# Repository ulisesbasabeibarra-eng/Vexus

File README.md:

# Triatlon-2026
Robot Triatlón para Bonaerenses 2026 por parte de los Alumnos de 6° año. **Campeones Región 2**

- [@Ulises Basabe](https://github.com/ulisesbasabeibarra-eng)
- [@Facundo Dominguez](https://github.com/facundodominguez1)
- [@Ramiro Trejo](https://github.com/RamiiTrejo)

## Componentes 

1-Esp32 38 pines

1-Bateria 2s de 450mAh

1-Bateria 3s de 1050mAh

2-Driver de motores BTS7960

2-Motores Titán de 1000RPM

## Sensores
1-Regleta **QTR8a** [Datasheet]()

3-Sensores infrarrojos **TCRT5000** [Datasheet]()

5-Sensores **Sharp Gp2y0a02yk0f**: [Datasheet]()

-3 frontales

-2 laterales

## PCB

Este PCB fue realizado con el software de diseño libre y gratuito KiCad, el cual nos facilita el uso debido a su interfaz intuitiva 

En este se implemento el diseño doble faz y componentes SMD (como lo son capacitores, una resitencia y un regulador)

## Modelo 3D

En este proyecto se utilizo Autodesk, plataforma de software, ademas de ser muy utilizado a la hora de hacer diseños 3D, gracias a que este ofrece una amplia gama de software como AutoCAD, Fusion 360, Inventor y 3ds Max, utilizados en sectores como la ingeniería, la arquitectura, el entretenimiento y el diseño de productos.

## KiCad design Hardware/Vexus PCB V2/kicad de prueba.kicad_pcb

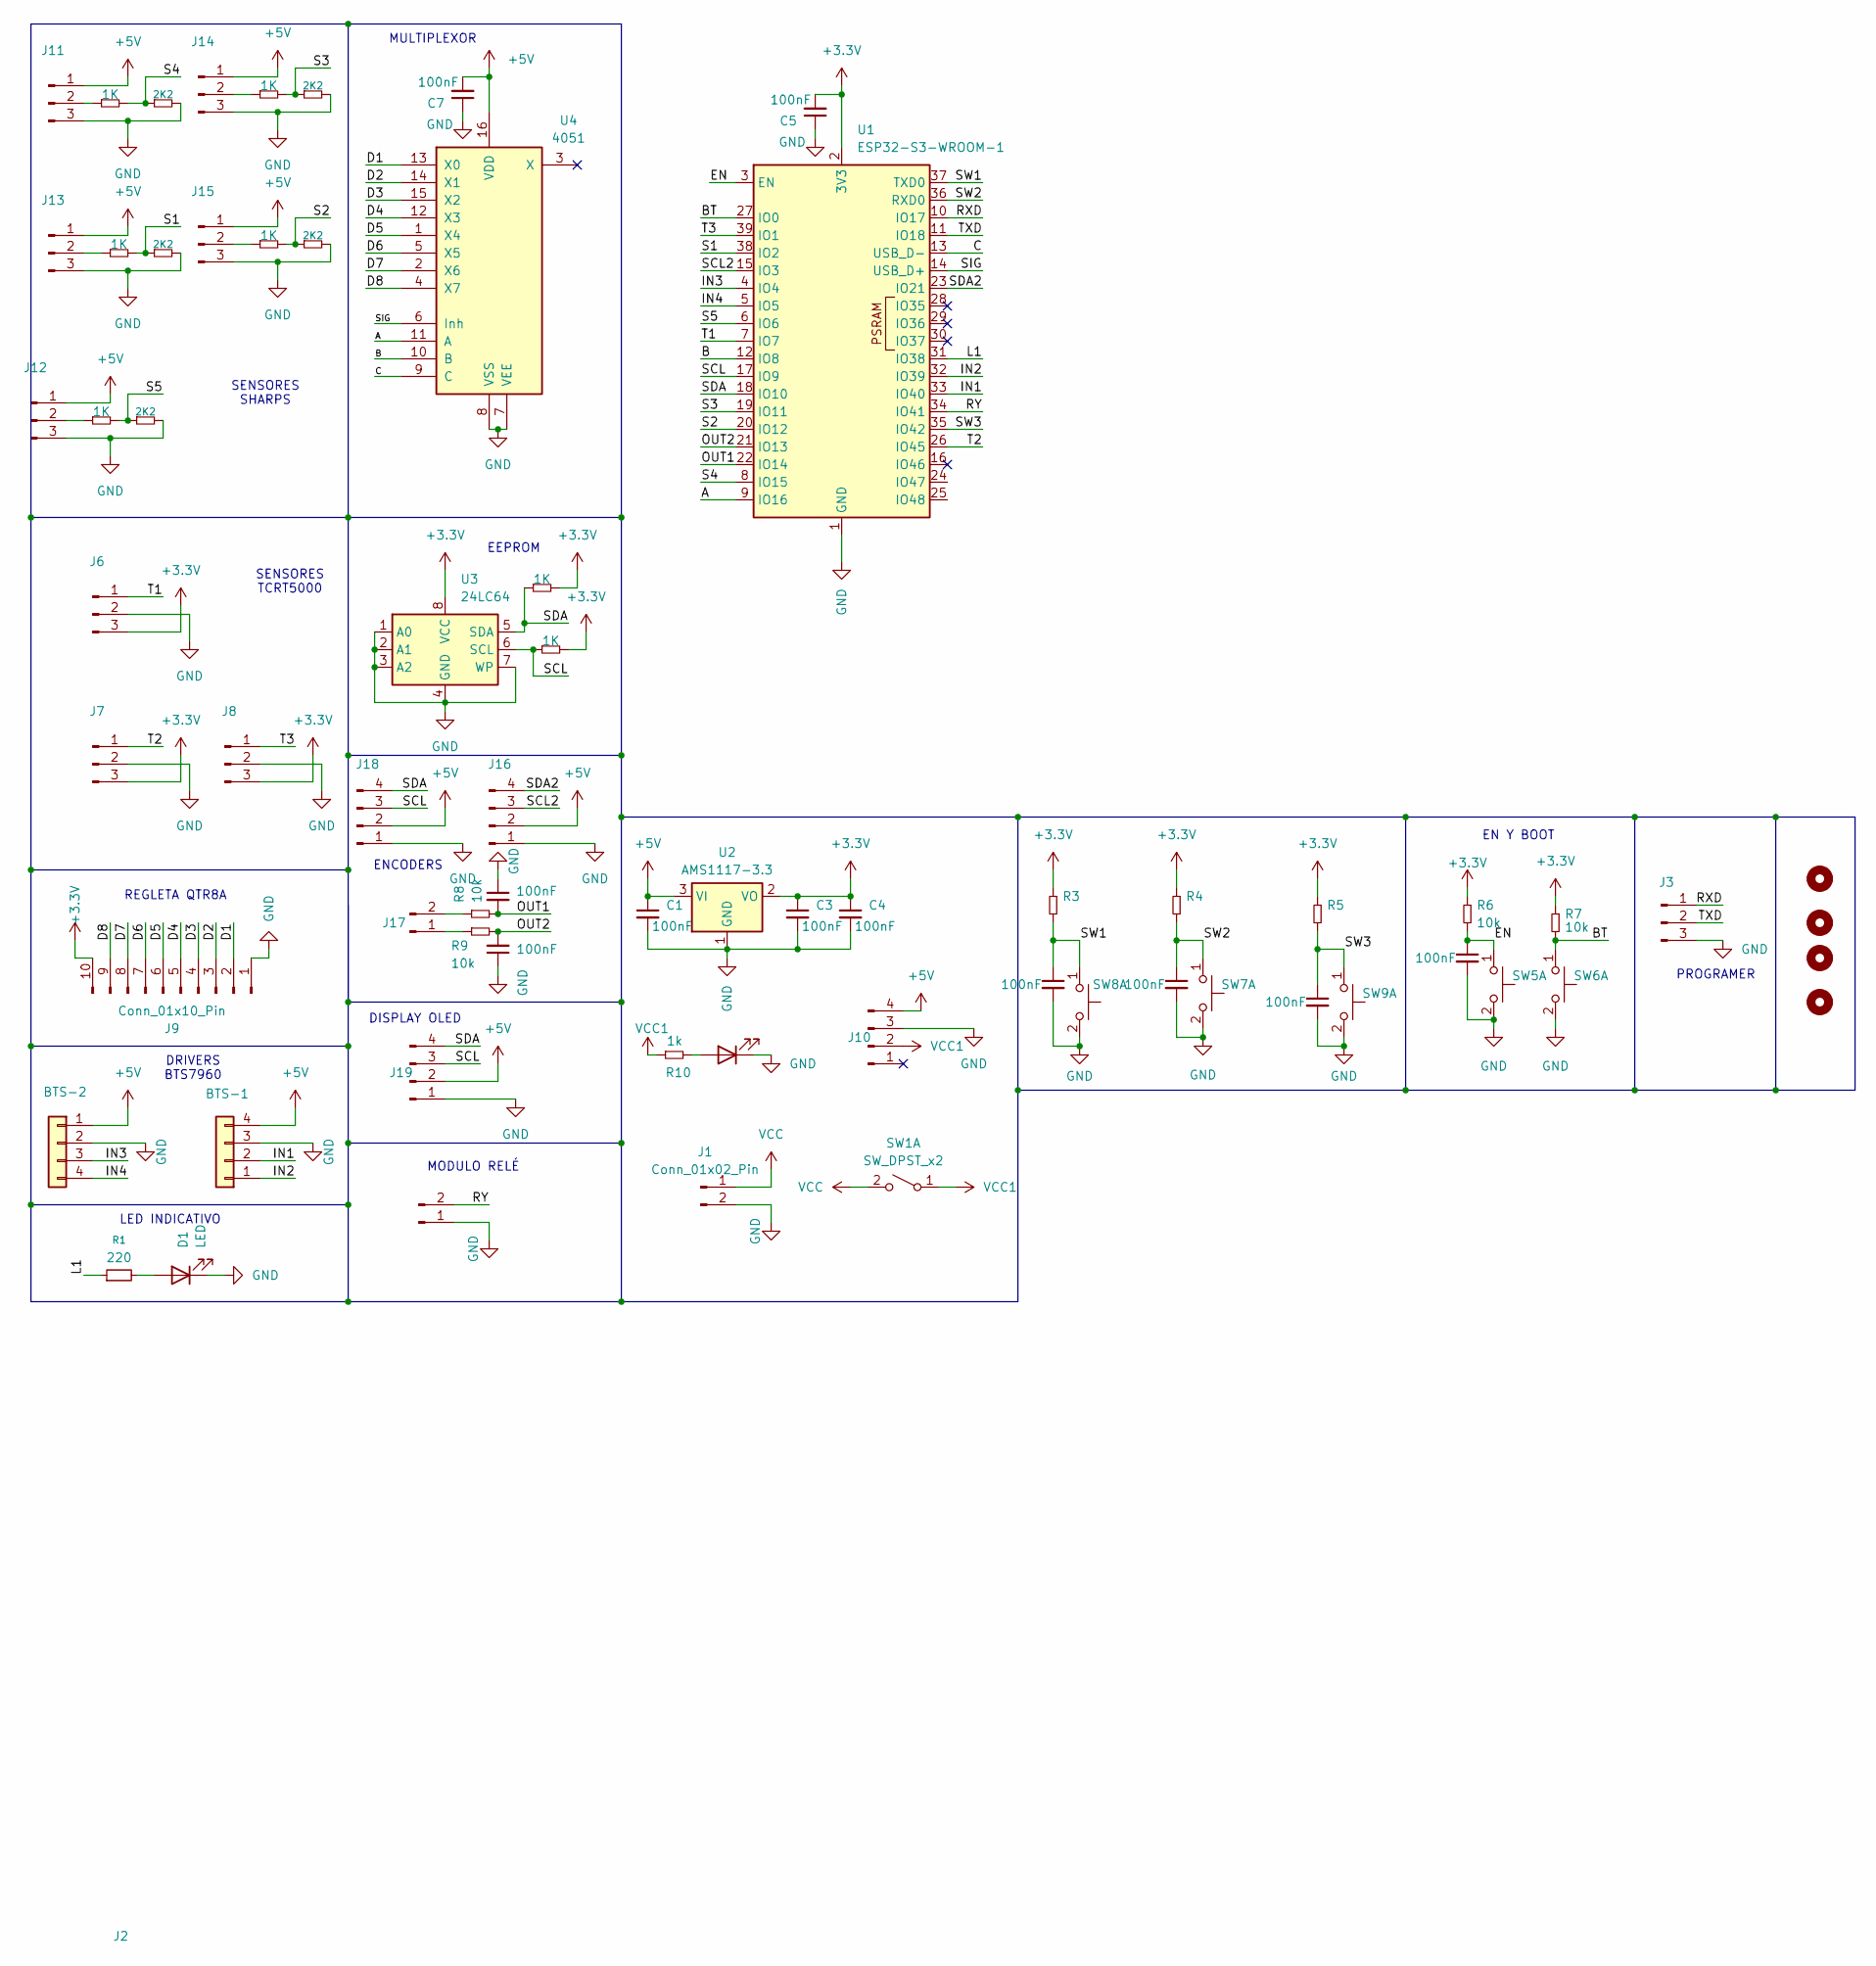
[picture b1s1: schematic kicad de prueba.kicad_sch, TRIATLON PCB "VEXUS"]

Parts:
C1, C3, C4, C5, C6, C7, C8, C9, C10, C11, C12: 100nF; C_0805_2012Metric_Pad1.18x1.45mm_HandSolder
D1, D2: LED; LED_0805_2012Metric_Pad1.15x1.40mm_HandSolder
H1, H2, H3, H4: MountingHole; MountingHole_3.2mm_M3_ISO7380
J1: Conn_01x02_Pin; AMASS_XT30PW-M_1x02_P2.50mm_Horizontal
J2: Conn_01x02_Pin; JST_XH_S2B-XH-A_1x02_P2.50mm_Horizontal
J3: Conn_01x03_Pin; PinHeader_1x03_P2.54mm_Vertical
J4: BTS-1; JST_XH_S4B-XH-A-1_1x04_P2.50mm_Horizontal
J5: BTS-2; JST_XH_S4B-XH-A-1_1x04_P2.50mm_Horizontal
J6, J7, J8, J11, J12, J13, J14, J15: Conn_01x03_Pin; JST_XH_S3B-XH-A-1_1x03_P2.50mm_Horizontal
J9: Conn_01x10_Pin; JST_XH_S10B-XH-A_1x10_P2.50mm_Horizontal
J10: Conn_01x04_Pin; Step_Down_Mini
J16, J18, J19: Conn_01x04_Pin; JST_XH_B4B-XH-A_1x04_P2.50mm_Vertical
J17: Conn_01x02_Pin; JST_XH_B2B-XH-A_1x02_P2.50mm_Vertical
R1: 220; R_0805_2012Metric_Pad1.20x1.40mm_HandSolder
R3, R4, R5, R6, R7, R8, R9: 10k; R_0805_2012Metric_Pad1.20x1.40mm_HandSolder
R10: 1k; R_0805_2012Metric_Pad1.20x1.40mm_HandSolder
R15, R16, R19, R21, R23, R25, R26: 1K; R_0805_2012Metric_Pad1.20x1.40mm_HandSolder
R17, R18, R20, R22, R24: 2K2; R_0805_2012Metric_Pad1.20x1.40mm_HandSolder
SW1: SW_DPST_x2; Switch Slide
SW5, SW6, SW7, SW8, SW9: SW_Push_Dual_x2; SW SMD 3.5X6X5
U1: ESP32-S3-WROOM-1
U2: AMS1117-3.3; SOT-223-3_TabPin2
U3: 24LC64; DIP-8_W7.62mm_LongPads
U4: 4051; SOIC-16_4.55x10.3mm_P1.27mm

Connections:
+3.3V: C3.1, C4.1, C5.2, J6.3, J7.3, J8.3, J9.10, R3.1, R4.1, R5.1, R6.1, R7.1, R25.2, R26.2, U1.2 (3V3), U2.2 (VO), U3.8 (VCC)
+5V: C1.1, C7.2, J4.4, J5.1, J10.4, J11.1, J12.1, J13.1, J14.1, J15.1, J16.2, J18.2, J19.2, U2.3 (VI), U4.16 (VDD)
/A: U1.9 (IO16), U4.11 (A)
/B: U1.12 (IO8), U4.10 (B)
/BT: R7.2, SW6.1 (C), U1.27 (IO0)
/C: U1.13 (USB_D-), U4.9 (C)
/D1: J9.2, U4.13 (X0)
/D2: J9.3, U4.14 (X1)
/D3: J9.4, U4.15 (X2)
/D4: J9.5, U4.12 (X3)
/D5: J9.6, U4.1 (X4)
/D6: J9.7, U4.5 (X5)
/D7: J9.8, U4.2 (X6)
/D8: J9.9, U4.4 (X7)
/EN: C6.1, R6.2, SW5.1 (C), U1.3 (EN)
/IN1: J4.2, U1.33 (IO40)
/IN2: J4.1, U1.32 (IO39)
/IN3: J5.3, U1.4 (IO4)
/IN4: J5.4, U1.5 (IO5)
/L1: R1.1, U1.31 (IO38)
/OUT1: C11.2, R8.2, U1.22 (IO14)
/OUT2: C12.2, R9.2, U1.21 (IO13)
/RXD: J3.1, U1.10 (IO17)
/RY: J2.2, U1.34 (IO41)
/S1: R23.2, R24.1, U1.38 (IO2)
/S2: R16.2, R18.1, U1.20 (IO12)
/S3: R19.2, R20.1, U1.19 (IO11)
/S4: R21.2, R22.1, U1.8 (IO15)
/S5: R15.2, R17.1, U1.6 (IO6)
/SCL: J18.3, J19.3, R26.1, U1.17 (IO9), U3.6 (SCL)
/SCL2: J16.3, U1.15 (IO3)
/SDA: J18.4, J19.4, R25.1, U1.18 (IO10), U3.5 (SDA)
/SDA2: J16.4, U1.23 (IO21)
/SIG: U1.14 (USB_D+), U4.6 (Inh)
/SW1: C10.1, R3.2, SW8.1 (C), U1.37 (TXD0)
/SW2: C9.1, R4.2, SW7.1 (C), U1.36 (RXD0)
/SW3: C8.1, R5.2, SW9.1 (C), U1.35 (IO42)
/T1: J6.1, U1.7 (IO7)
/T2: J7.1, U1.26 (IO45)
/T3: J8.1, U1.39 (IO1)
/TXD: J3.2, U1.11 (IO18)
GND: C1.2, C3.2, C4.2, C5.1, C6.2, C7.1, C8.2, C9.2, C10.2, C11.1, C12.1, D1.1 (K), D2.1 (K), J1.2, J2.1, J3.3, J4.3, J5.2, J6.2, J7.2, J8.2, J9.1, J10.3, J11.3, J12.3, J13.3, J14.3, J15.3, J16.1, J18.1, J19.1, R17.2, R18.2, R20.2, R22.2, R24.2, SW5.2 (D), SW6.2 (D), SW7.2 (D), SW8.2 (D), SW9.2 (D), U1.1 (GND), U1.40 (GND), U1.41 (GND), U2.1 (GND), U3.1 (A0), U3.2 (A1), U3.3 (A2), U3.4 (GND), U3.7 (WP), U4.7 (VEE), U4.8 (VSS)
unnamed: D1.2 (A), R1.2
unnamed: D2.2 (A), R10.2
unnamed: J11.2, R21.1
unnamed: J12.2, R15.1
unnamed: J13.2, R23.1
unnamed: J14.2, R19.1
unnamed: J15.2, R16.1
unnamed: J17.1, R9.1
unnamed: J17.2, R8.1
VCC: J1.1, SW1.2 (B)
VCC1: J10.2, R10.1, SW1.1 (A)

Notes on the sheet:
EEPROM
REGLETA QTR8A
SENSORES TCRT5000
DRIVERS BTS7960
LED INDICATIVO
PROGRAMER
SENSORES SHARPS
DISPLAY OLED
ENCODERS
MODULO RELÉ
MULTIPLEXOR
EN Y BOOT

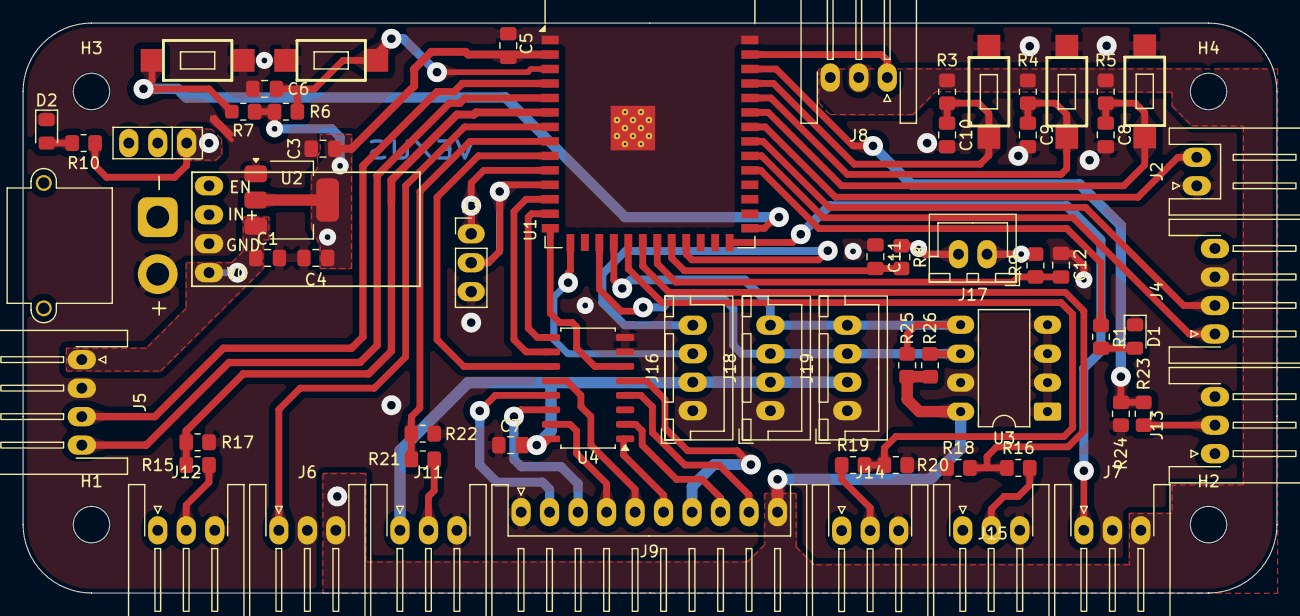
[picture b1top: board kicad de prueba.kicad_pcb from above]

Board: 2 copper layers, 110.0 x 50.0 mm, 67 parts (0 on the bottom side), 53 nets.

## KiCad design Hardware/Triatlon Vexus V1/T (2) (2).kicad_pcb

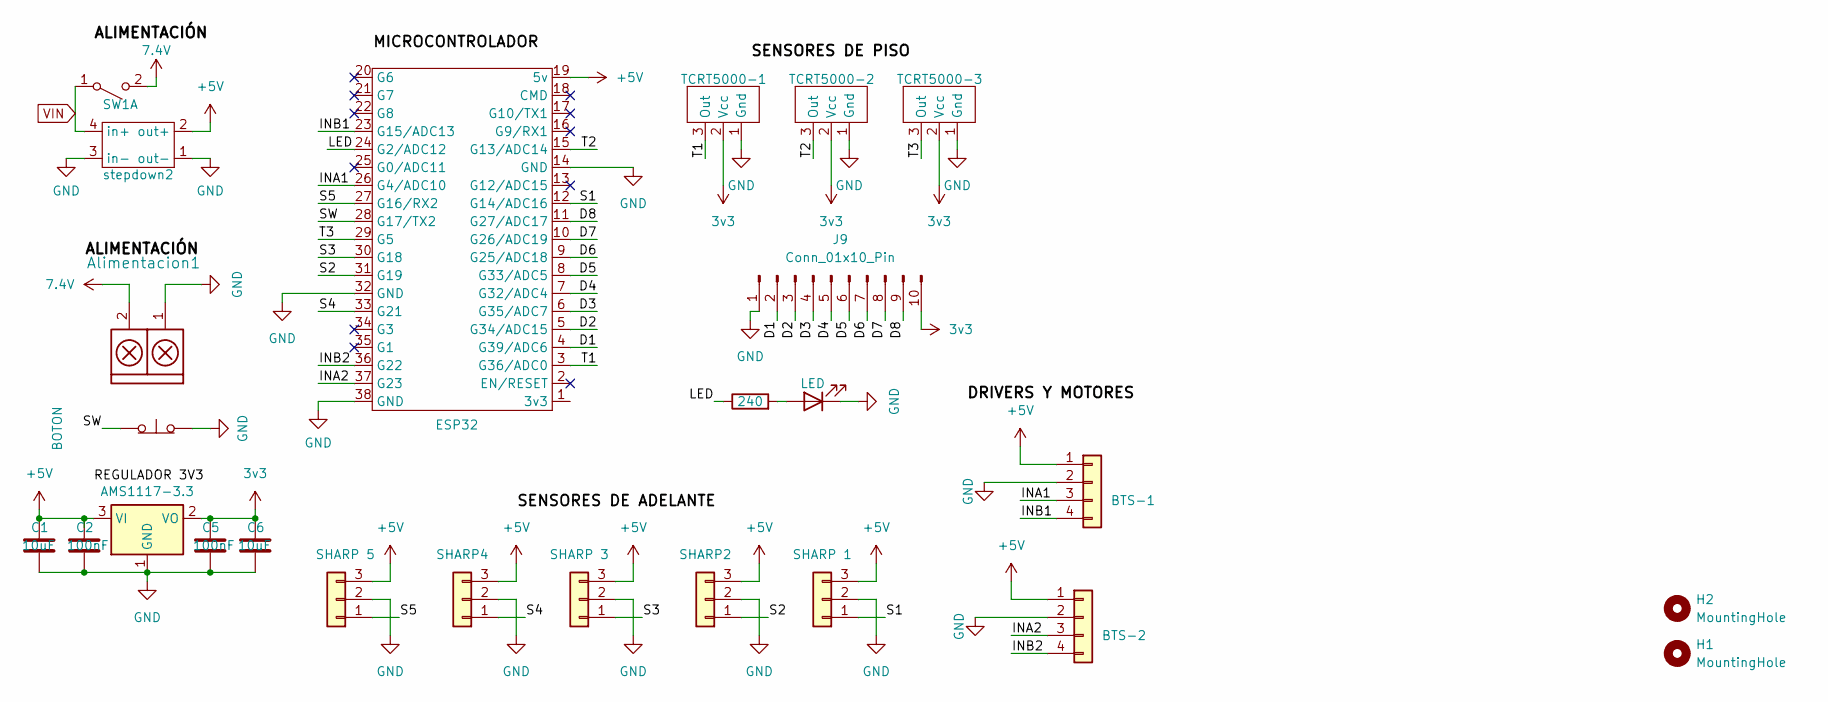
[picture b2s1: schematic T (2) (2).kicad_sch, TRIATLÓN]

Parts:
Alimentacion1: TB_1X2; AMASS_XT30PW-M_1x02_P2.50mm_Horizontal
C1, C6: 10uF; C_0805_2012Metric
C2, C5: 100nF; C_0805_2012Metric
D1: LED; LED_D5.0mm
ESP32: esp32 38 pin usb-c
H1, H2: MountingHole; MountingHole_3.2mm_M3_DIN965
J1: SHARP 1; JST_XH_S3B-XH-A-1_1x03_P2.50mm_Horizontal
J2: BTS-1; JST_XH_S4B-XH-A_1x04_P2.50mm_Horizontal
J3: SHARP2; JST_XH_S3B-XH-A-1_1x03_P2.50mm_Horizontal
J4: SHARP 3; JST_XH_S3B-XH-A-1_1x03_P2.50mm_Horizontal
J5: BTS-2; JST_XH_S4B-XH-A_1x04_P2.50mm_Horizontal
J7: SHARP 5; JST_XH_S3B-XH-A-1_1x03_P2.50mm_Horizontal
J8: SHARP4; JST_XH_S3B-XH-A-1_1x03_P2.50mm_Horizontal
J9: Conn_01x10_Pin; JST_XH_S10B-XH-A-1_1x10_P2.50mm_Horizontal
R1: 240; R_1206_3216Metric_Pad1.30x1.75mm_HandSolder
SW1: SW_DPST_x2; switch smd
SW2: BOTON; Button
TCRT5000-1, TCRT5000-2, TCRT5000-3: JST_XH_S3B-XH-A-1_1x03_P2.50mm_Horizontal
U2: AMS1117-3.3; SOT-223-3_TabPin2
stepdown2: STEPDOWN

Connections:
3v3: C5.1, C6.1, J9.10, TCRT5000-1.2 (Vcc), TCRT5000-2.2 (Vcc), TCRT5000-3.2 (Vcc), U2.2 (VO)
7.4V: Alimentacion1.2, SW1.2 (B)
+5V: C1.1, C2.1, ESP32.19 (5v), J1.3, J2.1, J3.3, J4.3, J5.1, J7.3, J8.3, U2.3 (VI), stepdown2.2 (out+)
/D1: ESP32.4 (G39/ADC6), J9.2
/D2: ESP32.5 (G34/ADC15), J9.3
/D3: ESP32.6 (G35/ADC7), J9.4
/D4: ESP32.7 (G32/ADC4), J9.5
/D5: ESP32.8 (G33/ADC5), J9.6
/D6: ESP32.9 (G25/ADC18), J9.7
/D7: ESP32.10 (G26/ADC19), J9.8
/D8: ESP32.11 (G27/ADC17), J9.9
/INA1: ESP32.26 (G4/ADC10), J2.3
/INA2: ESP32.37 (G23), J5.3
/INB1: ESP32.23 (G15/ADC13), J2.4
/INB2: ESP32.36 (G22), J5.4
/LED: ESP32.24 (G2/ADC12), R1.1
/S1: ESP32.12 (G14/ADC16), J1.1
/S2: ESP32.31 (G19), J3.1
/S3: ESP32.30 (G18), J4.1
/S4: ESP32.33 (G21), J8.1
/S5: ESP32.27 (G16/RX2), J7.1
/SW: ESP32.28 (G17/TX2), SW2.1 (A)
/T1: ESP32.3 (G36/ADC0), TCRT5000-1.3 (Out)
/T2: ESP32.15 (G13/ADC14), TCRT5000-2.3 (Out)
/T3: ESP32.29 (G5), TCRT5000-3.3 (Out)
GND: Alimentacion1.1, C1.2, C2.2, C5.2, C6.2, D1.1 (K), ESP32.14 (GND), ESP32.32 (GND), ESP32.38 (GND), J1.2, J2.2, J3.2, J4.2, J5.2, J7.2, J8.2, J9.1, SW2.2 (B), TCRT5000-1.1 (Gnd), TCRT5000-2.1 (Gnd), TCRT5000-3.1 (Gnd), U2.1 (GND), stepdown2.1 (out-), stepdown2.3 (in-)
unnamed: D1.2 (A), R1.2
VIN: SW1.1 (A), stepdown2.4 (in+)

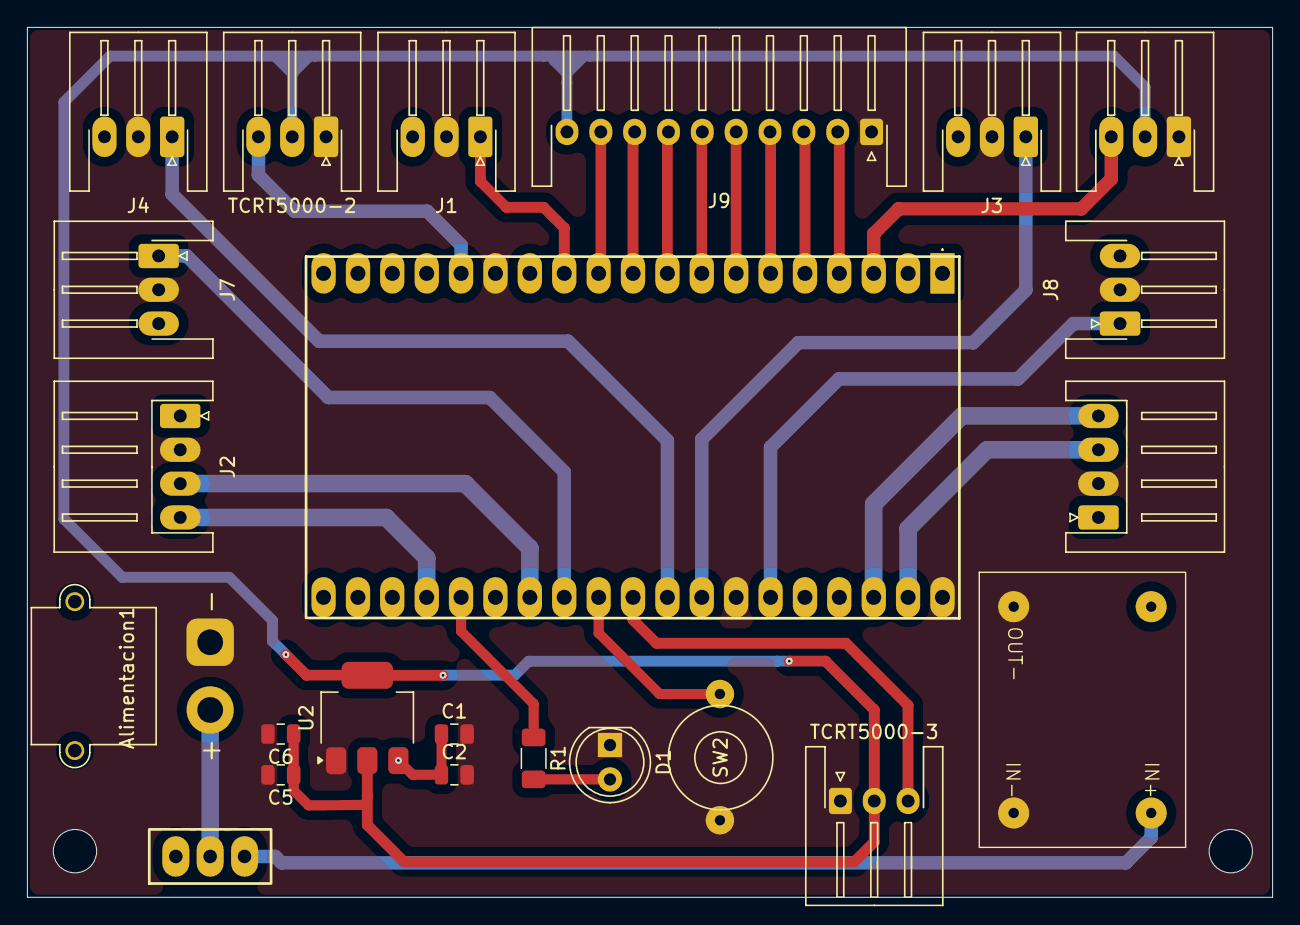
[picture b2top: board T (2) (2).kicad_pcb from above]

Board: 2 copper layers, 92.0 x 64.3 mm, 25 parts (0 on the bottom side), 28 nets.

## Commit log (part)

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2026-04-21 Refactor motor control and integrate QTR sensors
    Updated motor control logic and added QTR sensor integration.
2026-04-21 Update Pruebas
2026-04-24 Add new file 'a' in Vexus-v1 directory
2026-04-24 Add new file 'a' in Carroceria/Vexus-V2
2026-04-24 Add new file 'a' with initial content
2026-04-24 Add new file 'a' in Carroceria/Vexus-V1
2026-04-24 Organizacion de las versiones de vexus
2026-04-25 Create a
2026-04-25 Create 4
2026-05-02 Add new file 'a' in Velocista-without-QTRSensors
2026-05-02 src line follower-without-QTRSensors
    Removed QTRSensors library and related code. Updated PID constants and motor control logic.
2026-05-18 Enhance README with components and sensors details
    Added detailed components and sensors sections to the README.
2026-05-18 Update README with images for 3D model section
    Added images to the 3D model section in README.
